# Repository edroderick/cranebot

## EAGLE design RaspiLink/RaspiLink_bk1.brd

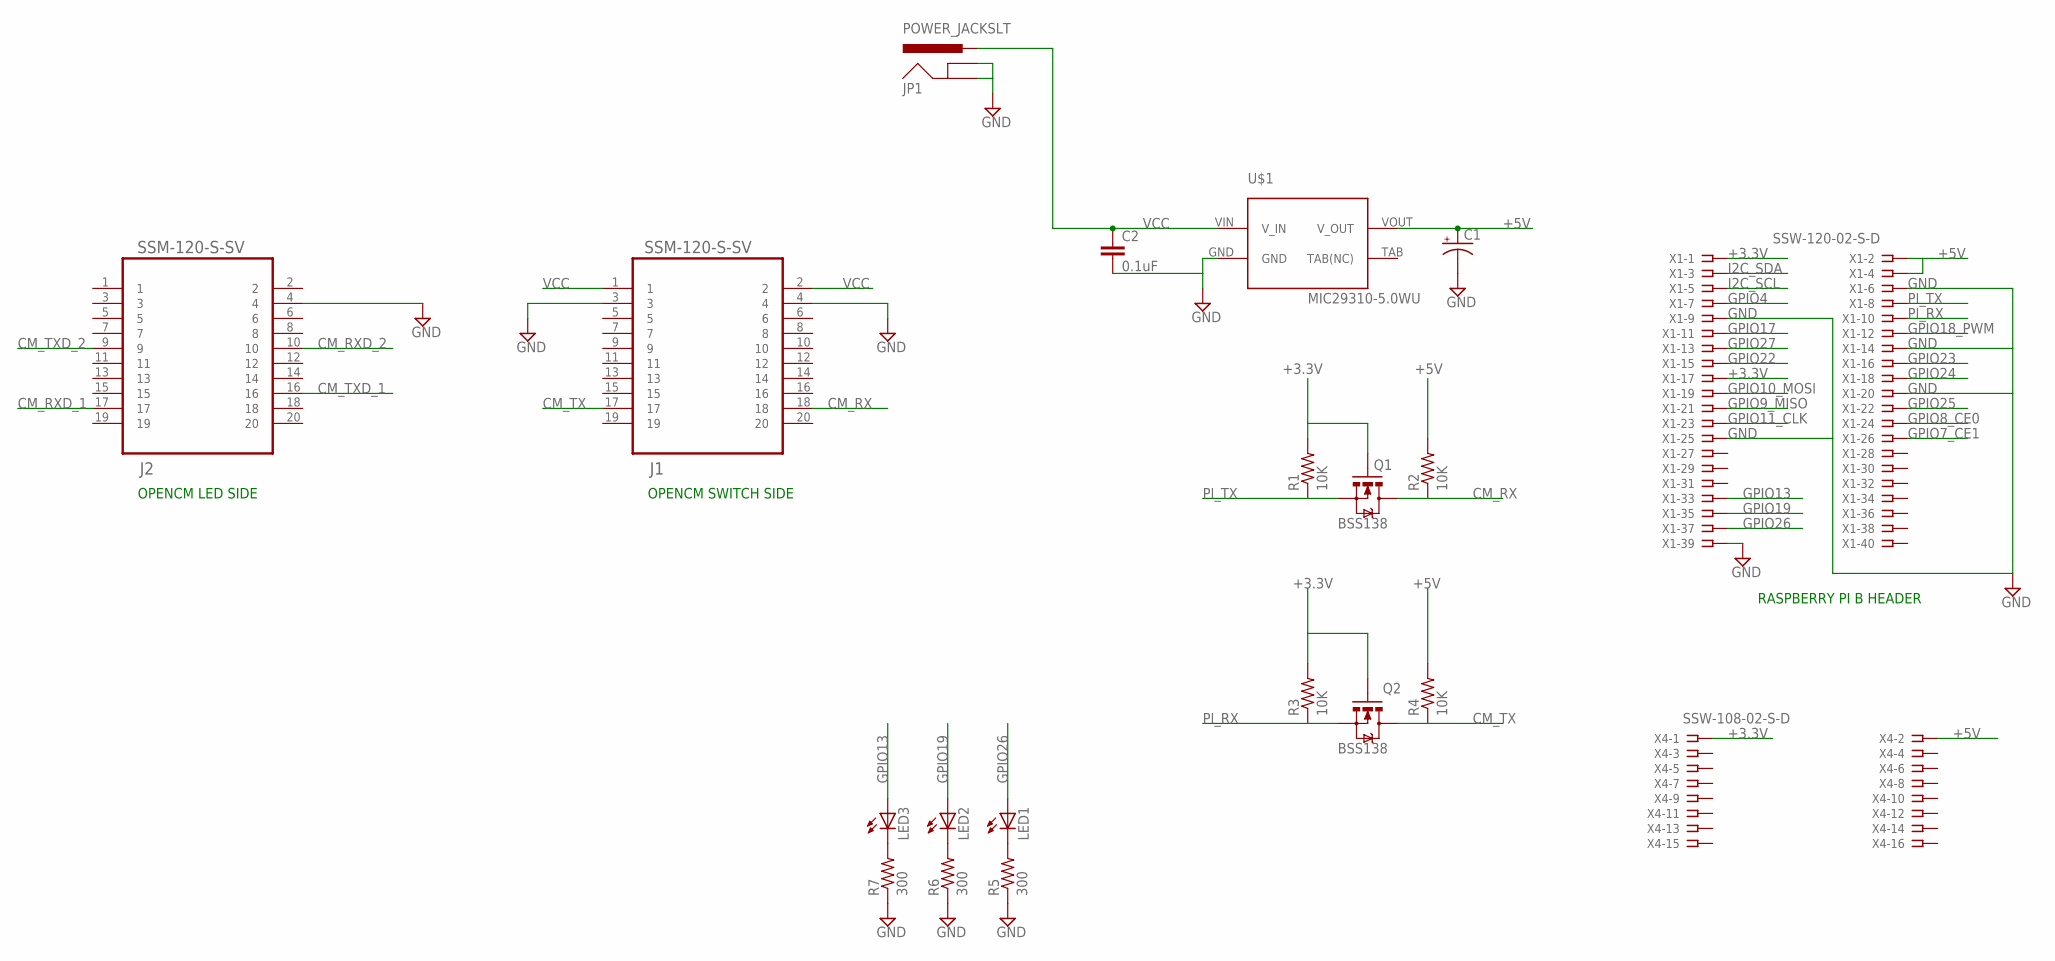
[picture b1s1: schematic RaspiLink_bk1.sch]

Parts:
C1: 100UF-25V-20%(PTH); CPOL-RADIAL-100UF-25V
C2: 0.1uF; 0603-CAP
J1, J2: SSM-120-S-SV; SAMTEC_SSM-120-S-SV
JP1: POWER_JACKSLT; POWER_JACK_SLOT
LED1, LED2, LED3: LED_ELD260; LED_LD260
Q1, Q2: MOSFET-NCHANNELBSS123LT1G; SOT23-3
R1, R2, R3, R4: 10K; 0603-RES
R5, R6, R7: 300; 0603-RES
U$1: MIC29310-5.0WU; TO-263-3
X1: SSW-120-02-S-D
X4: SSW-108-02-S-D

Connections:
+3.3V: Q1.1 (G), Q2.1 (G), R1.2, R3.2, X1.1, X1.17, X4.1
+5V: C1.1 (+), R2.2, R4.2, U$1.VOUT (V_OUT), X1.2, X1.4, X4.2
CM_RX: J1.18, Q1.3 (D), R2.1
CM_RXD_1: J2.17
CM_RXD_2: J2.10
CM_TX: J1.17, Q2.3 (D), R4.1
CM_TXD_1: J2.16
CM_TXD_2: J2.9
GND: C1.2 (-), C2.2, J1.3, J1.4, J2.4, JP1.GND@1 (GNDBREAK), JP1.GND@2 (GND), R5.1, R6.1, R7.1, U$1.GND, X1.6, X1.9, X1.14, X1.20, X1.25, X1.39
GPIO4: X1.7
GPIO7_CE1: X1.26
GPIO8_CE0: X1.24
GPIO9_MISO: X1.21
GPIO10_MOSI: X1.19
GPIO11_CLK: X1.23
GPIO13: LED3.A, X1.33
GPIO17: X1.11
GPIO18_PWM: X1.12
GPIO19: LED2.A, X1.35
GPIO22: X1.15
GPIO23: X1.16
GPIO24: X1.18
GPIO25: X1.22
GPIO26: LED1.A, X1.37
GPIO27: X1.13
I2C_SCL: X1.5
I2C_SDA: X1.3
unnamed: LED1.K (C), R5.2
unnamed: LED2.K (C), R6.2
unnamed: LED3.K (C), R7.2
PI_RX: Q2.2 (S), R3.1, X1.10
PI_TX: Q1.2 (S), R1.1, X1.8
VCC: C2.1, J1.1, J1.2, JP1.PWR, U$1.VIN (V_IN)

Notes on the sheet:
RASPBERRY PI B HEADER
OPENCM SWITCH SIDE
OPENCM LED SIDE

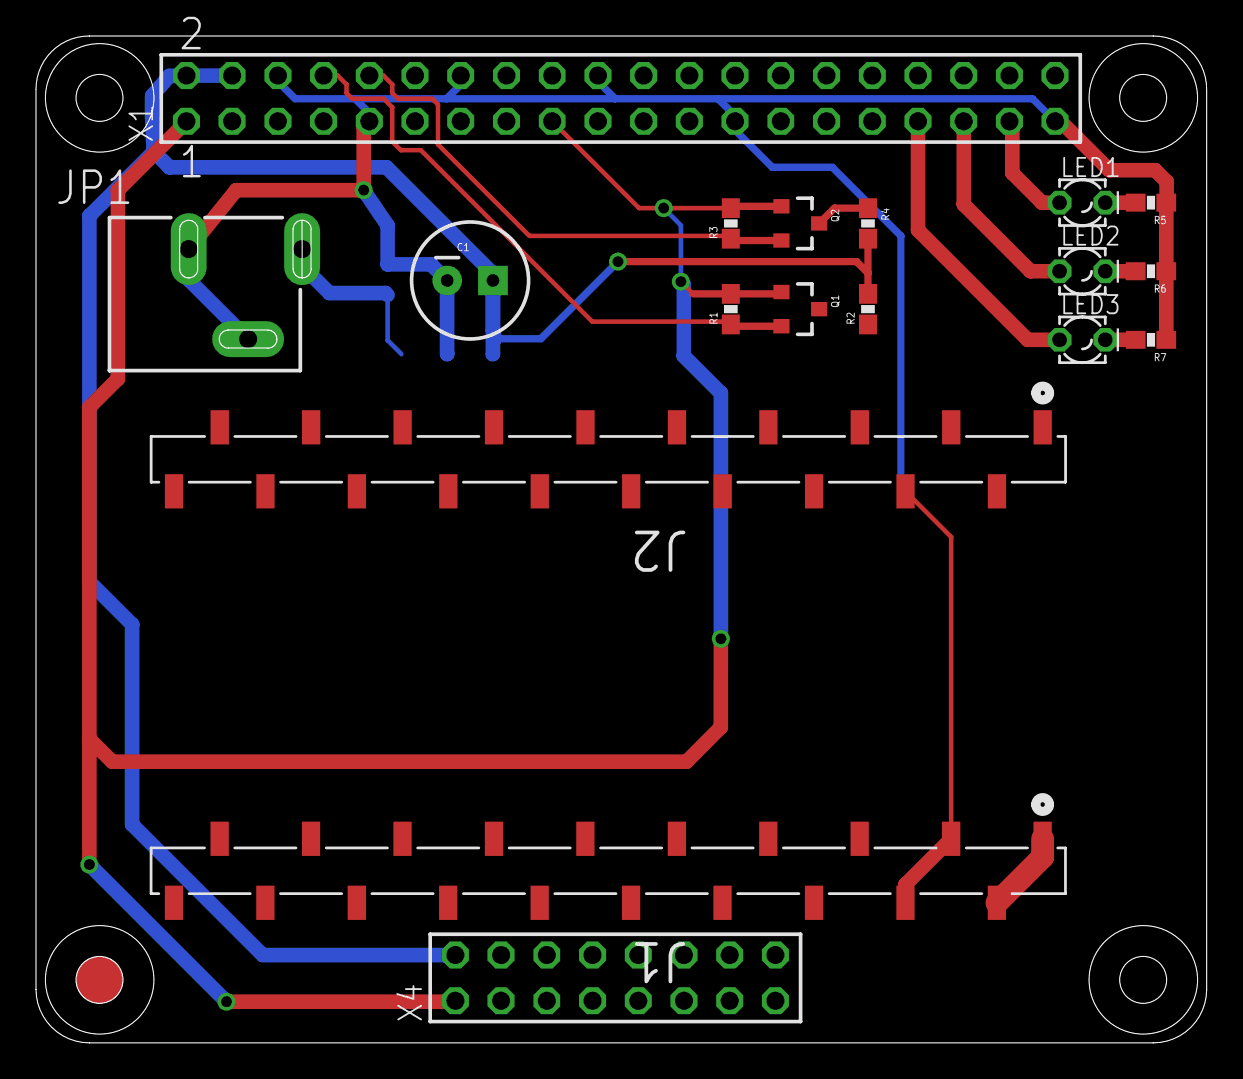
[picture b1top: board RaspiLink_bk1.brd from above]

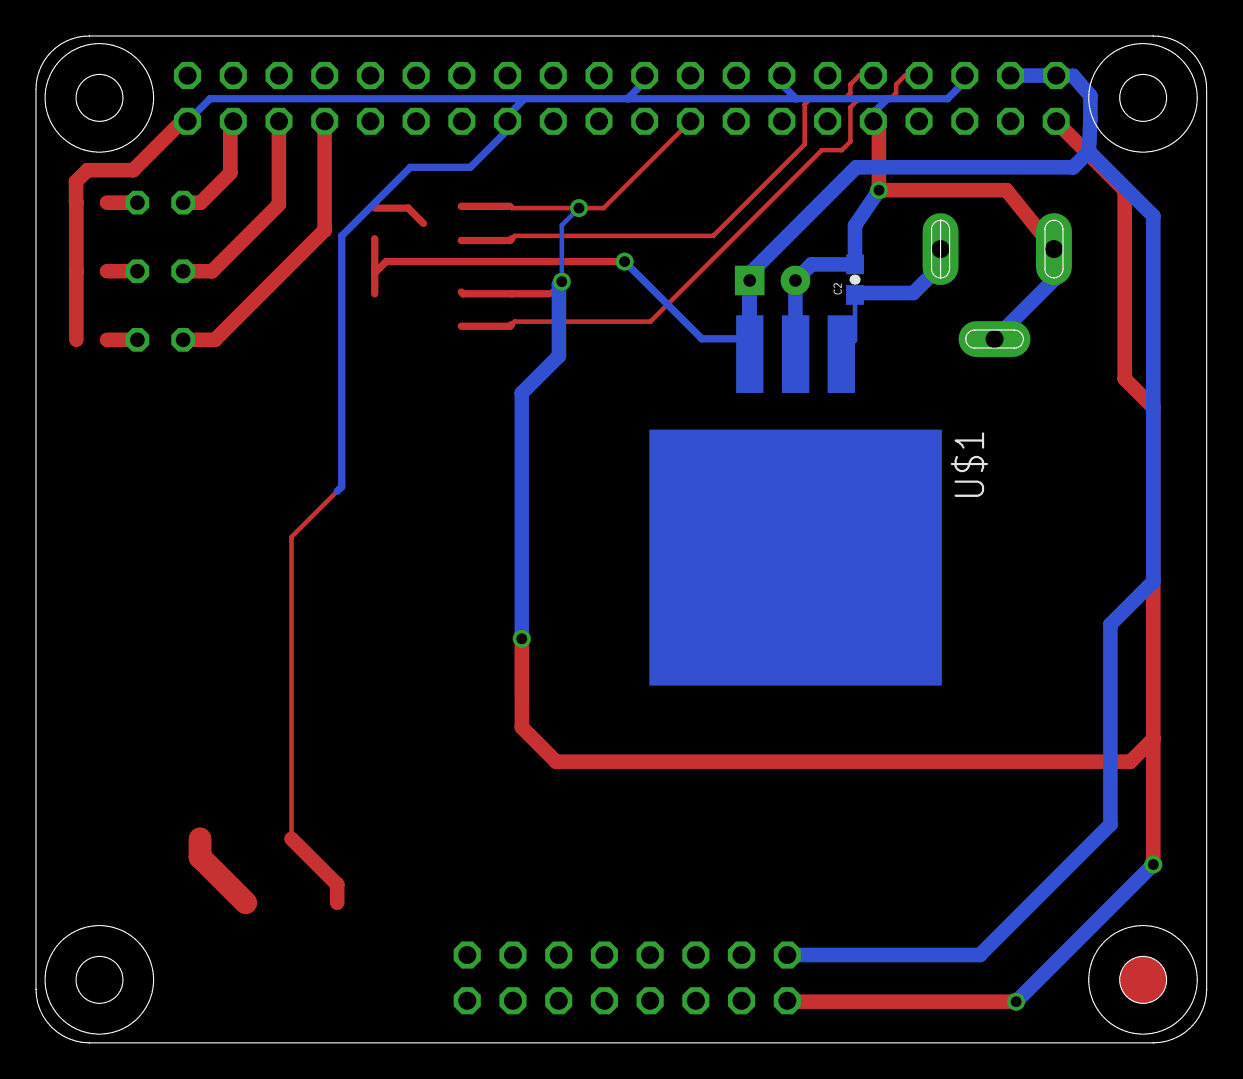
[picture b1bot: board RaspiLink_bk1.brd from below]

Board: 2 copper layers, 65.0 x 55.9 mm, 20 parts (2 on the bottom side), 14 nets.

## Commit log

2015-04-09 test
2015-04-09 working getInput
2015-04-09 working test night before
2015-04-09 receive changes from pi
2015-04-09 updates from lab
2015-04-09 lofaro edit
2015-04-22 pcb file
2015-04-22 pcb files
2015-04-23 joystick basecode
2015-04-23 joystick for crane
2015-04-29 edited code
2015-05-13 final commit

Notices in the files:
parts and their libraries:
SparkFun-DiscreteSemi: Licensing: Creative Commons ShareAlike 4.0 International - https://creativecommons.org/licenses/by-sa/4.0
